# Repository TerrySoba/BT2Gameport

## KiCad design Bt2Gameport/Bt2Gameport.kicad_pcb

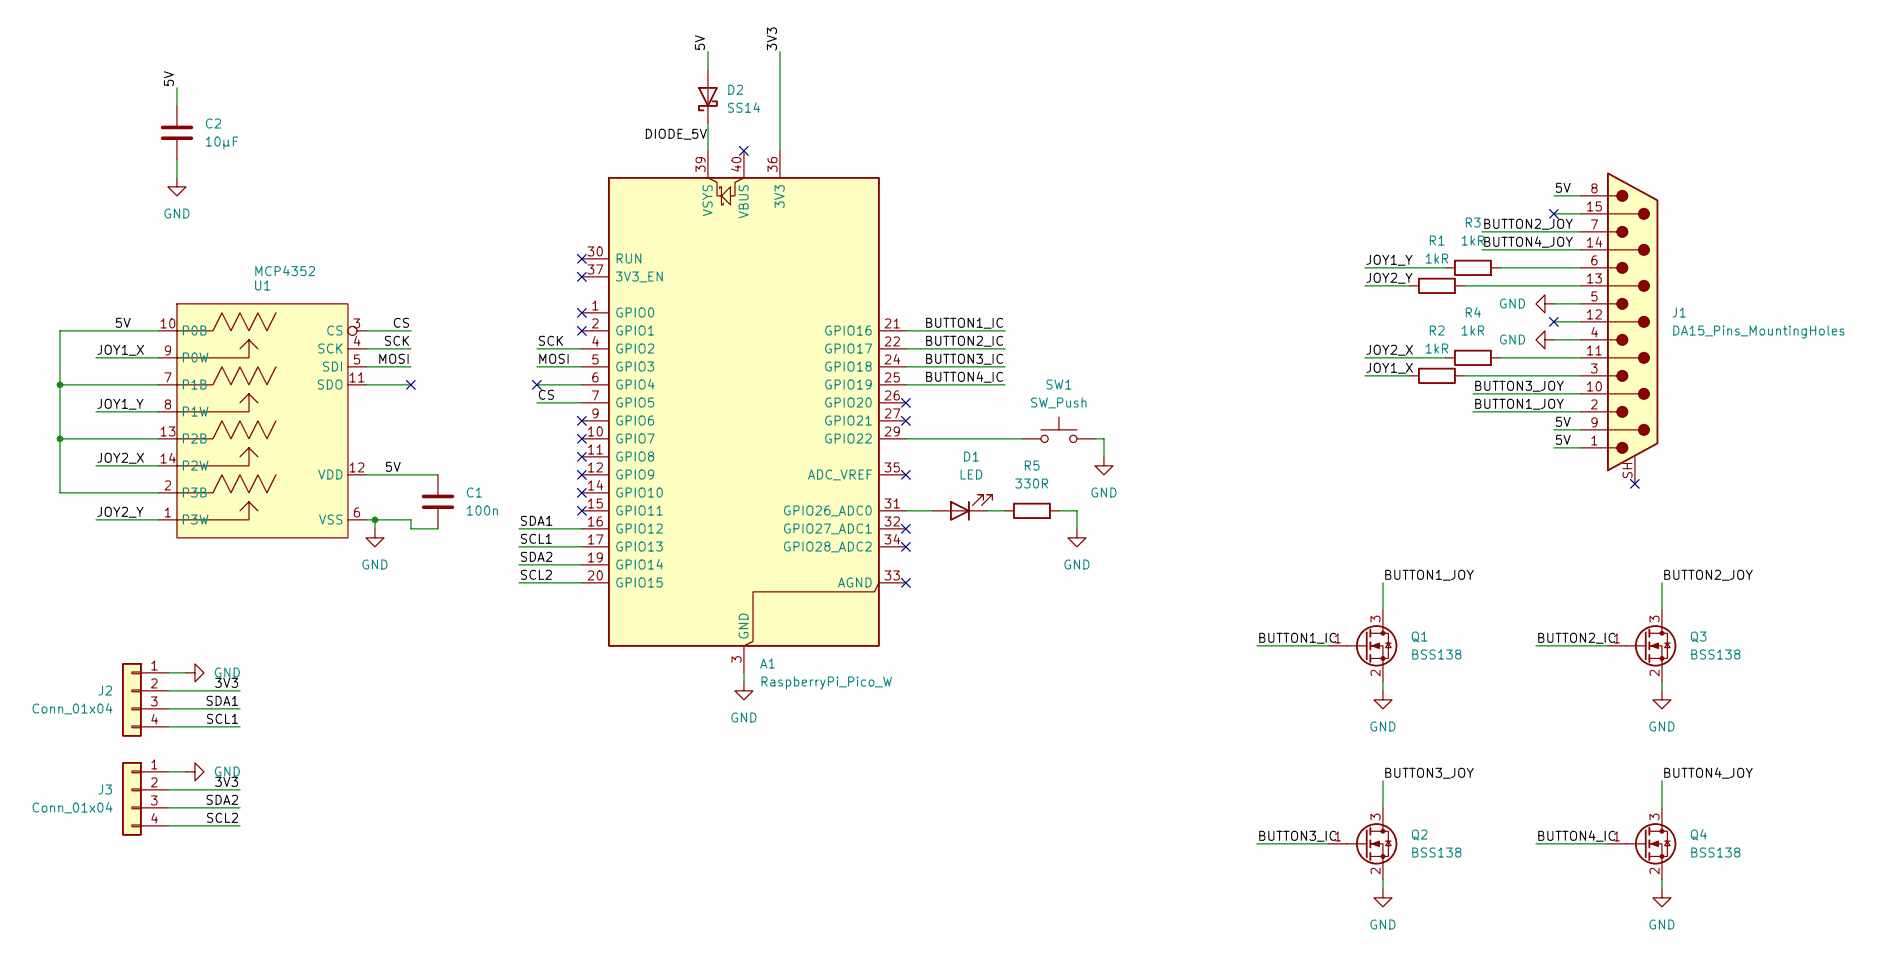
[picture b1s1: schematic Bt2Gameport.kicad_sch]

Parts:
A1: RaspberryPi_Pico_W; RaspberryPi_Pico_W_SMD_HandSolder
C1: 100n; C_0805_2012Metric_Pad1.18x1.45mm_HandSolder
C2: 10µF; C_0805_2012Metric_Pad1.18x1.45mm_HandSolder
D1: LED; LED_0805_2012Metric_Pad1.15x1.40mm_HandSolder
D2: SS14; D_SMA
J1: DA15_Pins_MountingHoles; DSUB-15_Pins_Horizontal_P2.77x2.84mm_EdgePinOffset7.70mm_Ho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
J2, J3: Conn_01x04; JST_SH_BM04B-SRSS-TB_1x04-1MP_P1.00mm_Vertical
Q1, Q2, Q3, Q4: BSS138; SOT-23
R1, R2, R3, R4: 1kR; R_0805_2012Metric_Pad1.20x1.40mm_HandSolder
R5: 330R; R_0805_2012Metric_Pad1.20x1.40mm_HandSolder
SW1: SW_Push; SW_Tactile_SPST_Angled_PTS645Vx83-2LFS
U1: MCP4352; TSSOP-14_4.4x5mm_P0.65mm

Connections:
/3V3: A1.36 (3V3), J2.2, J3.2
/5V: C1.1, C2.1, D2.2 (A), J1.1, J1.8, J1.9, U1.2 (P3B), U1.7 (P1B), U1.10 (P0B), U1.12 (VDD), U1.13 (P2B)
/BUTTON1_IC: A1.21 (GPIO16), Q1.1 (G)
/BUTTON1_JOY: J1.2, Q1.3 (D)
/BUTTON2_IC: A1.22 (GPIO17), Q3.1 (G)
/BUTTON2_JOY: J1.7, Q3.3 (D)
/BUTTON3_IC: A1.24 (GPIO18), Q2.1 (G)
/BUTTON3_JOY: J1.10, Q2.3 (D)
/BUTTON4_IC: A1.25 (GPIO19), Q4.1 (G)
/BUTTON4_JOY: J1.14, Q4.3 (D)
/CS: A1.7 (GPIO5), U1.3 (CS)
/DIODE_5V: A1.39 (VSYS), D2.1 (K)
/JOY1_X: R2.2, U1.9 (P0W)
/JOY1_Y: R3.1, U1.8 (P1W)
/JOY2_X: R4.1, U1.14 (P2W)
/JOY2_Y: R1.1, U1.1 (P3W)
/MOSI: A1.5 (GPIO3), U1.5 (SDI)
/SCK: A1.4 (GPIO2), U1.4 (SCK)
/SCL1: A1.17 (GPIO13), J2.4
/SCL2: A1.20 (GPIO15), J3.4
/SDA1: A1.16 (GPIO12), J2.3
/SDA2: A1.19 (GPIO14), J3.3
GND: A1.3 (GND), A1.8 (GND), A1.13 (GND), A1.18 (GND), A1.23 (GND), A1.28 (GND), A1.38 (GND), C1.2, C2.2, J1.4, J1.5, J2.1, J3.1, Q1.2 (S), Q2.2 (S), Q3.2 (S), Q4.2 (S), R5.2, SW1.2, U1.6 (VSS)
unnamed: A1.29 (GPIO22), SW1.1
unnamed: A1.31 (GPIO26_ADC0), D1.2 (A)
unnamed: D1.1 (K), R5.1
unnamed: J1.13, R1.2
unnamed: J1.11 (P111), R4.2
unnamed: J1.3, R2.1
unnamed: J1.6, R3.2

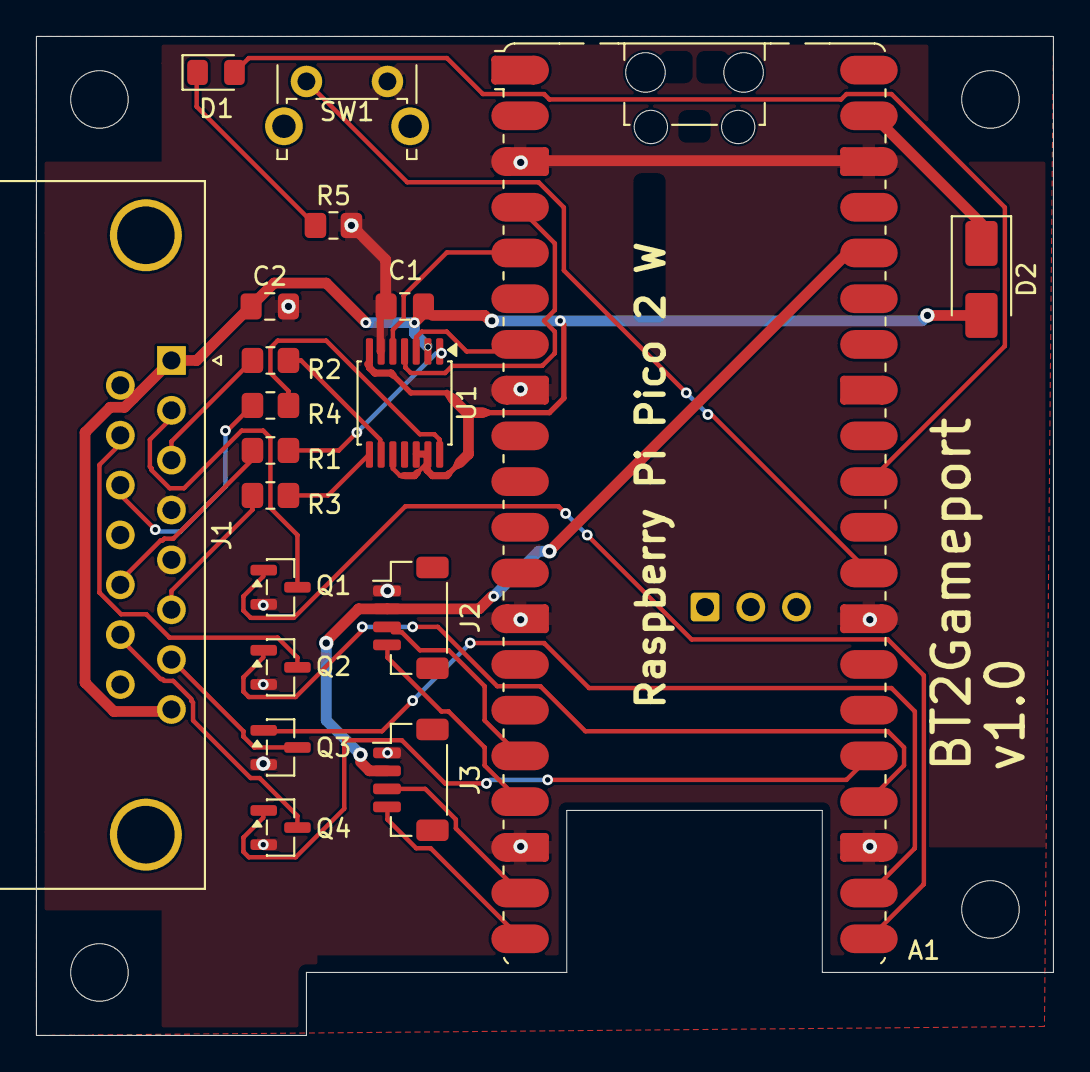
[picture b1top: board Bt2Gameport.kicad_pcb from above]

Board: 2 copper layers, 56.5 x 55.5 mm, 19 parts (0 on the bottom side), 30 nets.
